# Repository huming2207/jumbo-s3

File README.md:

# jumbo-s3

PoC hardware design of ESP32-S3FN8 + 16MB (APS12808L-3OBM-BA) PSRAM

## Intro

As of September 2022, Espressif doesn't provide an official solution for ESP32-S3 that comes with more than 8MB PSRAM. However someone mentioned that the APS12808L works with ESP32-S3 but no open source design.

Therefore here comes my solution. It has been proven working fine. No modification needed for ESP-IDF. As long as the PSRAM support is enabled and set to octal mode, 80MHz, it should just works.

## Log

Here's a simple boot log that runs the APS12808L in octal SPI mode at 80MHz, and logs the free heap size.

```
ESP-ROM:esp32s3-20210327
Build:Mar 27 2021
rst:0x1 (POWERON),boot:0x8 (SPI_FAST_FLASH_BOOT)
SPIWP:0xee
mode:DIO, clock div:1
load:0x3fce3810,len:0x1808
load:0x403c9700,len:0xd6c
load:0x403cc700,len:0x2ed4
entry 0x403c992c
I (24) boot: ESP-IDF v5.1-dev-862-g09f7589ef2 2nd stage bootloader
I (25) boot: compile time Sep 20 2022 23:02:14
I (25) boot: chip revision: V001
I (29) boot_comm: chip revision: 1, min. bootloader chip revision: 0
I (36) qio_mode: Enabling default flash chip QIO
I (42) boot.esp32s3: Boot SPI Speed : 80MHz
I (46) boot.esp32s3: SPI Mode       : QIO
I (51) boot.esp32s3: SPI Flash Size : 4MB
I (56) boot: Enabling RNG early entropy source...
I (61) boot: Partition Table:
I (65) boot: ## Label            Usage          Type ST Offset   Length
I (72) boot:  0 nvs              WiFi data        01 02 00009000 00006000
I (79) boot:  1 phy_init         RF data          01 01 0000f000 00001000
I (87) boot:  2 factory          factory app      00 00 00010000 00100000
I (94) boot: End of partition table
I (99) boot_comm: chip revision: 1, min. application chip revision: 0
I (106) esp_image: segment 0: paddr=00010020 vaddr=3c020020 size=08a5ch ( 35420) map
I (120) esp_image: segment 1: paddr=00018a84 vaddr=3fc92700 size=03268h ( 12904) load
I (125) esp_image: segment 2: paddr=0001bcf4 vaddr=40374000 size=04324h ( 17188) load
I (135) esp_image: segment 3: paddr=00020020 vaddr=42000020 size=196fch (104188) map
I (155) esp_image: segment 4: paddr=00039724 vaddr=40378324 size=0a30ch ( 41740) load
I (164) esp_image: segment 5: paddr=00043a38 vaddr=50000000 size=00010h (    16) load
I (170) boot: Loaded app from partition at offset 0x10000
I (170) boot: Disabling RNG early entropy source...
I (184) octal_psram: vendor id    : 0x0d (AP)
I (184) octal_psram: dev id       : 0x02 (generation 3)
I (184) octal_psram: density      : 0x05 (128 Mbit)
I (189) octal_psram: good-die     : 0x01 (Pass)
I (195) octal_psram: Latency      : 0x01 (Fixed)
I (200) octal_psram: VCC          : 0x01 (3V)
I (205) octal_psram: SRF          : 0x01 (Fast Refresh)
I (211) octal_psram: BurstType    : 0x01 (Hybrid Wrap)
I (217) octal_psram: BurstLen     : 0x01 (32 Byte)
I (222) octal_psram: Readlatency  : 0x02 (10 cycles@Fixed)
I (228) octal_psram: DriveStrength: 0x00 (1/1)
W (233) PSRAM: DO NOT USE FOR MASS PRODUCTION! Timing parameters will be updated in future IDF version.
I (244) esp_psram: Found 16MB PSRAM device
I (248) esp_psram: Speed: 80MHz
I (252) cpu_start: Pro cpu up.
I (256) cpu_start: Starting app cpu, entry point is 0x40375378
I (0) cpu_start: App cpu up.
I (1167) esp_psram: SPI SRAM memory test OK
I (1176) cpu_start: Pro cpu start user code
I (1176) cpu_start: cpu freq: 160000000 Hz
I (1176) cpu_start: Application information:
I (1179) cpu_start: Project name:     main
I (1184) cpu_start: App version:      1
I (1188) cpu_start: Compile time:     Sep 20 2022 23:02:12
I (1195) cpu_start: ELF file SHA256:  1f3449a15147ac7a...
Warning: checksum mismatch between flashed and built applications. Checksum of built application is e6bd8ac9c4e022dd86afd168d00707482f76b53ee256de9e101a4846cd271af5
I (1201) cpu_start: ESP-IDF:          v5.1-dev-862-g09f7589ef2
I (1207) heap_init: Initializing. RAM available for dynamic allocation:
I (1215) heap_init: At 3FC963E8 len 00053328 (332 KiB): D/IRAM
I (1221) heap_init: At 3FCE9710 len 00005724 (21 KiB): STACK/DRAM
I (1228) heap_init: At 3FCF0000 len 00008000 (32 KiB): DRAM
I (1234) heap_init: At 600FE010 len 00001FF0 (7 KiB): RTCRAM
I (1241) esp_psram: Adding pool of 16384K of PSRAM memory to heap allocator
I (1249) spi_flash: detected chip: gd
I (1253) spi_flash: flash io: qio
W (1257) spi_flash: Detected size(8192k) larger than the size in the binary image header(4096k). Using the size in the binary image header.
I (1270) cpu_start: Starting scheduler on PRO CPU.
I (0) cpu_start: Starting scheduler on APP CPU.
I (1290) esp_psram: Reserving pool of 32K of internal memory for DMA/internal allocations
I (1290) test: Lay hou
I (1300) test: Max heap: 17117304

```

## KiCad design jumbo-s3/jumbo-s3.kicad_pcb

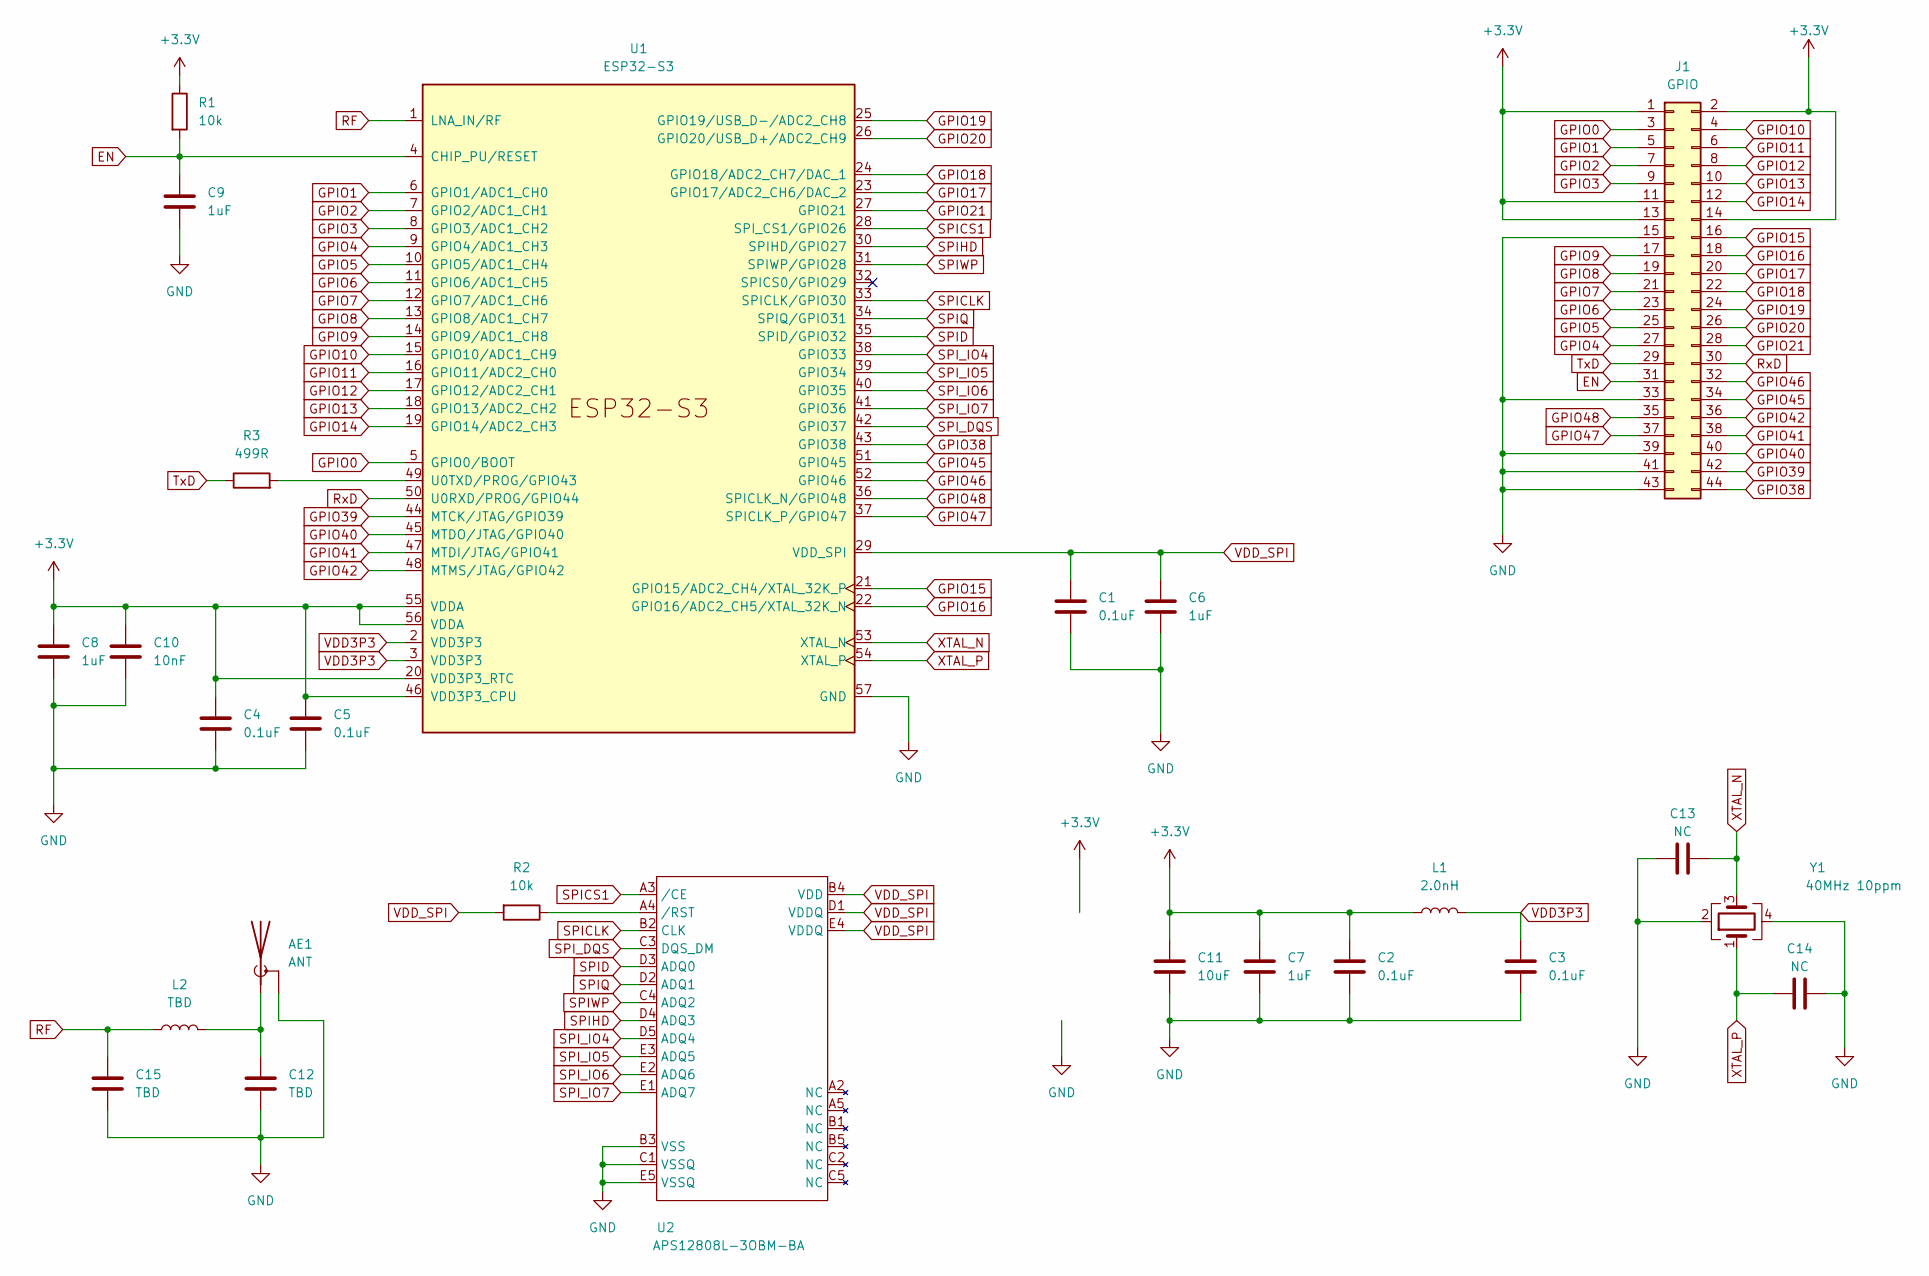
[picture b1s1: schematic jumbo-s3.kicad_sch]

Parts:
AE1: ANT; Texas_SWRA117D_2.4GHz_Left
C1, C2, C3, C4, C5: 0.1uF; C_0603_1608Metric_Pad1.08x0.95mm_HandSolder
C6, C7, C8, C9: 1uF; C_0603_1608Metric_Pad1.08x0.95mm_HandSolder
C10: 10nF; C_0603_1608Metric_Pad1.08x0.95mm_HandSolder
C11: 10uF; C_0603_1608Metric_Pad1.08x0.95mm_HandSolder
C12, C15: TBD; C_0603_1608Metric_Pad1.08x0.95mm_HandSolder
C13, C14: NC; C_0603_1608Metric_Pad1.08x0.95mm_HandSolder
J1: GPIO; PinHeader_2x22_P1.27mm_Vertical_SMD
L1: 2.0nH; L_0603_1608Metric_Pad1.05x0.95mm_HandSolder
L2: TBD; L_0603_1608Metric_Pad1.05x0.95mm_HandSolder
R1, R2: 10k; R_0603_1608Metric_Pad0.98x0.95mm_HandSolder
R3: 499R; R_0603_1608Metric_Pad0.98x0.95mm_HandSolder
U1: ESP32-S3; QFN-56-1EP_7x7mm_P0.4mm_EP5.6x5.6mm
U2: APS12808L-3OBM-BA; MINIBGA-24L
Y1: 40MHz 10ppm; Crystal_SMD_3225-4Pin_3.2x2.5mm_HandSoldering

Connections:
+3.3V: C2.1, C4.1, C5.1, C7.1, C8.2, C10.2, C11.1, J1.1, J1.2, J1.11, J1.13, J1.14, L1.1, R1.1, U1.20 (VDD3P3_RTC), U1.46 (VDD3P3_CPU), U1.55 (VDDA), U1.56 (VDDA)
EN: C9.1, J1.31, R1.2, U1.4 (CHIP_PU/RESET)
GND: AE1.2 (Shield), C1.2, C2.2, C3.2, C4.2, C5.2, C6.2, C7.2, C8.1, C9.2, C10.1, C11.2, C12.2, C13.1, C14.2, C15.1, J1.15, J1.33, J1.39, J1.41, J1.43, U1.57 (GND), U2.B3 (VSS), U2.C1 (VSSQ), U2.E5 (VSSQ), Y1.2, Y1.4
GPIO0: J1.3, U1.5 (GPIO0/BOOT)
GPIO1: J1.5, U1.6 (GPIO1/ADC1_CH0)
GPIO2: J1.7, U1.7 (GPIO2/ADC1_CH1)
GPIO3: J1.9, U1.8 (GPIO3/ADC1_CH2)
GPIO4: J1.27, U1.9 (GPIO4/ADC1_CH3)
GPIO5: J1.25, U1.10 (GPIO5/ADC1_CH4)
GPIO6: J1.23, U1.11 (GPIO6/ADC1_CH5)
GPIO7: J1.21, U1.12 (GPIO7/ADC1_CH6)
GPIO8: J1.19, U1.13 (GPIO8/ADC1_CH7)
GPIO9: J1.17, U1.14 (GPIO9/ADC1_CH8)
GPIO10: J1.4, U1.15 (GPIO10/ADC1_CH9)
GPIO11: J1.6, U1.16 (GPIO11/ADC2_CH0)
GPIO12: J1.8, U1.17 (GPIO12/ADC2_CH1)
GPIO13: J1.10, U1.18 (GPIO13/ADC2_CH2)
GPIO14: J1.12, U1.19 (GPIO14/ADC2_CH3)
GPIO15: J1.16, U1.21 (GPIO15/ADC2_CH4/XTAL_32K_P)
GPIO16: J1.18, U1.22 (GPIO16/ADC2_CH5/XTAL_32K_N)
GPIO17: J1.20, U1.23 (GPIO17/ADC2_CH6/DAC_2)
GPIO18: J1.22, U1.24 (GPIO18/ADC2_CH7/DAC_1)
GPIO19: J1.24, U1.25 (GPIO19/USB_D-/ADC2_CH8)
GPIO20: J1.26, U1.26 (GPIO20/USB_D+/ADC2_CH9)
GPIO21: J1.28, U1.27 (GPIO21)
GPIO38: J1.44, U1.43 (GPIO38)
GPIO39: J1.42, U1.44 (MTCK/JTAG/GPIO39)
GPIO40: J1.40, U1.45 (MTDO/JTAG/GPIO40)
GPIO41: J1.38, U1.47 (MTDI/JTAG/GPIO41)
GPIO42: J1.36, U1.48 (MTMS/JTAG/GPIO42)
GPIO45: J1.34, U1.51 (GPIO45)
GPIO46: J1.32, U1.52 (GPIO46)
GPIO47: J1.37, U1.37 (SPICLK_P/GPIO47)
GPIO48: J1.35, U1.36 (SPICLK_N/GPIO48)
unnamed: AE1.1 (A), C12.1, L2.2
unnamed: R2.1, U2.A4 (/RST)
unnamed: R3.2, U1.49 (U0TXD/PROG/GPIO43)
RF: C15.2, L2.1, U1.1 (LNA_IN/RF)
RxD: J1.30, U1.50 (U0RXD/PROG/GPIO44)
SPICLK: U1.33 (SPICLK/GPIO30), U2.B2 (CLK)
SPICS1: U1.28 (SPI_CS1/GPIO26), U2.A3 (/CE)
SPID: U1.35 (SPID/GPIO32), U2.D3 (ADQ0)
SPIHD: U1.30 (SPIHD/GPIO27), U2.D4 (ADQ3)
SPIQ: U1.34 (SPIQ/GPIO31), U2.D2 (ADQ1)
SPIWP: U1.31 (SPIWP/GPIO28), U2.C4 (ADQ2)
SPI_DQS: U1.42 (GPIO37), U2.C3 (DQS_DM)
SPI_IO4: U1.38 (GPIO33), U2.D5 (ADQ4)
SPI_IO5: U1.39 (GPIO34), U2.E3 (ADQ5)
SPI_IO6: U1.40 (GPIO35), U2.E2 (ADQ6)
SPI_IO7: U1.41 (GPIO36), U2.E1 (ADQ7)
TxD: J1.29, R3.1
VDD3P3: C3.1, L1.2, U1.2 (VDD3P3), U1.3 (VDD3P3)
VDD_SPI: C1.1, C6.1, R2.2, U1.29 (VDD_SPI), U2.B4 (VDD), U2.D1 (VDDQ), U2.E4 (VDDQ)
XTAL_N: C13.2, U1.53 (XTAL_N), Y1.3
XTAL_P: C14.1, U1.54 (XTAL_P), Y1.1

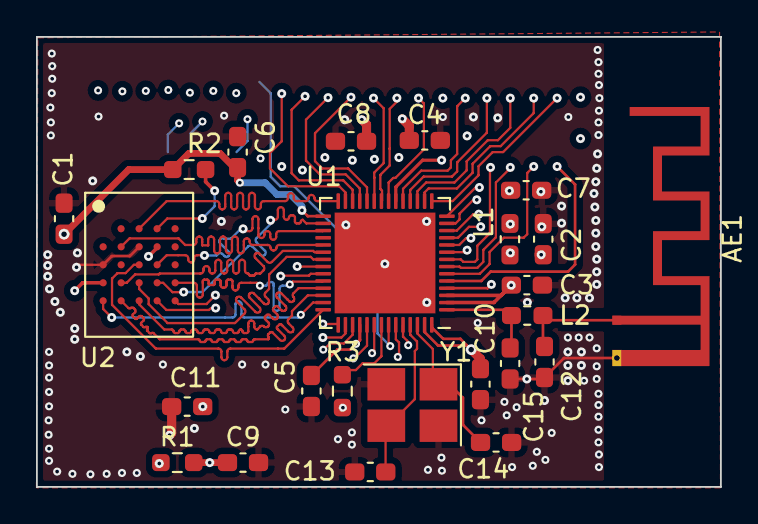
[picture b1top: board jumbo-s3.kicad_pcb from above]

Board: 4 copper layers, 38.0 x 25.0 mm, 25 parts (1 on the bottom side), 55 nets.

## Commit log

2022-08-31 Init
2022-08-31 Update submodule
2022-08-31 Add footprint & symbol ref
2022-09-01 schematic: add uC, flash and PSRAM
2022-09-02 Finish schematic
2022-09-03 pcb: rev. 1
2022-09-03 pcb: add rev 1 panel
2022-09-03 pcb: add rev 1 panel gerber
2022-09-06 Update schematic PDF
2022-09-21 Rev 2: init
2022-09-21 rev2: pcb: connect everything up
2022-09-21 rev2: finalise PCB
2022-09-21 rev2: pcb: final adjustments
2022-09-21 rev2: generate panels
2022-09-21 Rev 2.1: unify headers
2022-09-21 rev 2.1: fix warnings
2022-09-22 Rev 2.1: final fixes
2022-09-22 Rev 2.1: add panelised PCB/gerber
